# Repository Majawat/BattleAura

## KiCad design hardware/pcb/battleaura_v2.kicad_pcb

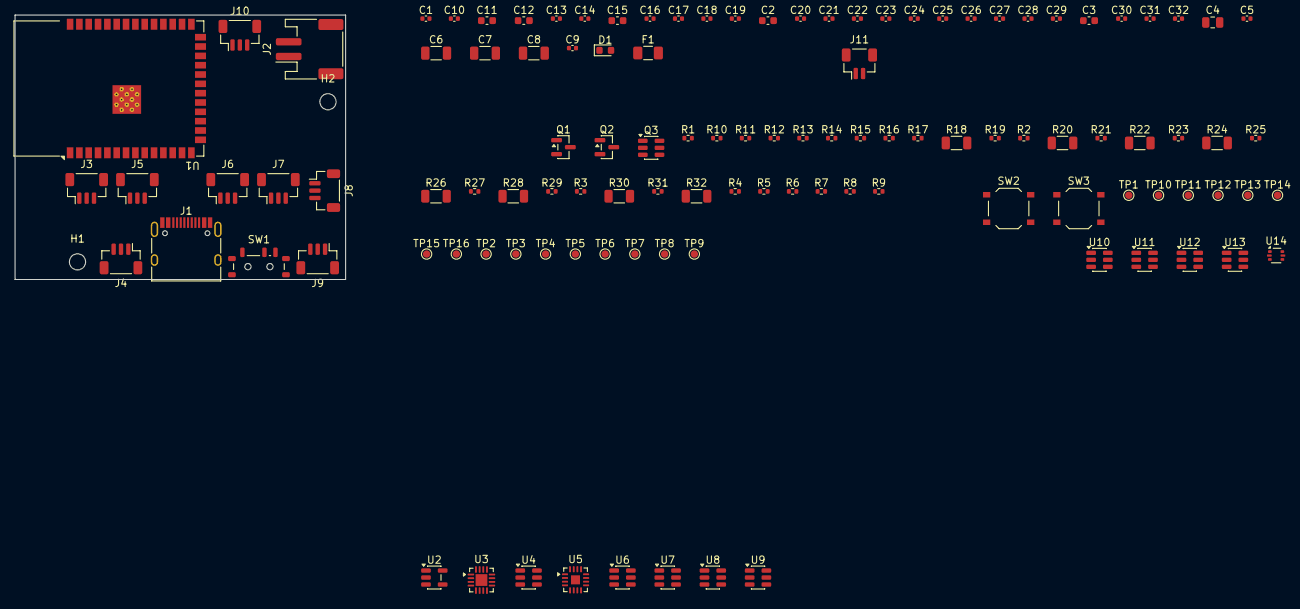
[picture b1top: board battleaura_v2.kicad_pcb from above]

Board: 2 copper layers, 45.0 x 36.0 mm, 115 parts (0 on the bottom side), 73 nets, no tracks yet.

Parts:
C1, C9, C13, C16, C17, C18, C19, C20, C21, C22, C23, C24, C25, C26, C27, C28, C29, C30, C31, C32: 100n; C_0402_1005Metric
C2, C3, C12, C15: 10u; C_0603_1608Metric
C4: 22u; C_0805_2012Metric
C5, C10, C14: 1u; C_0402_1005Metric
C6, C7, C8: 100u 10V; C_1206_3216Metric
C11: 22u; C_0603_1608Metric
D1: red; LED_0603_1608Metric
F1: 0.75A hold; Fuse_1206_3216Metric
H1, H2: MountingHole_2.2mm_M2
J1: USB_C_Receptacle_USB2.0_16P; USB_C_Receptacle_HRO_TYPE-C-31-M-12
J2: BATT; JST_PH_S2B-PH-SM4-TB_1x02-1MP_P2.00mm_Horizontal
J3: Z1; JST_SH_BM03B-SRSS-TB_1x03-1MP_P1.00mm_Vertical
J4: Z2; JST_SH_BM03B-SRSS-TB_1x03-1MP_P1.00mm_Vertical
J5: Z3; JST_SH_BM03B-SRSS-TB_1x03-1MP_P1.00mm_Vertical
J6: Z4; JST_SH_BM03B-SRSS-TB_1x03-1MP_P1.00mm_Vertical
J7: Z5; JST_SH_BM03B-SRSS-TB_1x03-1MP_P1.00mm_Vertical
J8: Z6; JST_SH_BM03B-SRSS-TB_1x03-1MP_P1.00mm_Vertical
J9: Z7; JST_SH_BM03B-SRSS-TB_1x03-1MP_P1.00mm_Vertical
J10: Z8; JST_SH_BM03B-SRSS-TB_1x03-1MP_P1.00mm_Vertical
J11: SPEAKER; JST_SH_BM02B-SRSS-TB_1x02-1MP_P1.00mm_Vertical
Q1, Q2: AO3401A; SOT-23
Q3: FS8205A; SOT-23-6
R1: 100; R_0402_1005Metric
R2, R10, R16: 1k; R_0402_1005Metric
R3, R4: 5.1k; R_0402_1005Metric
R5: 1.8k; R_0402_1005Metric
R6: 1.1k; R_0402_1005Metric
R7, R13: 10k; R_0402_1005Metric
R8: 1M; R_0402_1005Metric
R9, R12, R14, R15, R17, R19, R21, R23, R25, R27, R29, R31: 100k; R_0402_1005Metric
R11: 200k; R_0402_1005Metric
R18, R20, R22, R24, R26, R28, R30, R32: 120; R_1206_3216Metric
SW1: SW_SPDT; SW_SPDT_Shouhan_MSK12C02
SW2: BOOT; SW_Push_1P1T_XKB_TS-1187A
SW3: RESET; SW_Push_1P1T_XKB_TS-1187A
TP1: TXD0; TestPoint_Pad_D1.0mm
TP2: RXD0; TestPoint_Pad_D1.0mm
TP3: 3V3; TestPoint_Pad_D1.0mm
TP4: GND; TestPoint_Pad_D1.0mm
TP5: EN; TestPoint_Pad_D1.0mm
TP6: IO0; TestPoint_Pad_D1.0mm
TP7: IO3; TestPoint_Pad_D1.0mm
TP8: IO18; TestPoint_Pad_D1.0mm
TP9: IO21; TestPoint_Pad_D1.0mm
TP10: IO38; TestPoint_Pad_D1.0mm
TP11: IO39; TestPoint_Pad_D1.0mm
TP12: IO40; TestPoint_Pad_D1.0mm
TP13: IO41; TestPoint_Pad_D1.0mm
TP14: IO42; TestPoint_Pad_D1.0mm
TP15: IO47; TestPoint_Pad_D1.0mm
TP16: IO48; TestPoint_Pad_D1.0mm
U1: ESP32-S3-WROOM-1-N16R8; ESP32-S3-WROOM-1
U2: TLV75733PDBV; SOT-23-5
U3: BQ24074RGT; VQFN-16-1EP_3x3mm_P0.5mm_EP1.6x1.6mm
U4: DW01A; SOT-23-6
U5: MAX98357A; TQFN-16-1EP_3x3mm_P0.5mm_EP1.23x1.23mm
U6, U7, U8, U9, U10, U11, U12, U13: SN74LVC1T45DBV; SOT-23-6
U14: USBLC6-2SC6; SOT-666

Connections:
+3V3: C11.1, C12.1, C13.1, C17.1, C19.1, C21.1, C23.1, C25.1, C27.1, C29.1, C31.1, R13.2, R14.2, R15.2, TP3.1, U1.2, U2.5, U6.1, U6.5, U7.1, U7.5, U8.1, U8.5, U9.1, U9.5, U10.1, U10.5, U11.1, U11.5, U12.1, U12.5, U13.1, U13.5
CELL_N: C1.2, J2.2, Q1.1, Q3.1, U4.6
CELL_P: J2.1, Q1.3
CHG_N: R14.1, U1.17, U3.9
EN: C14.1, R13.1, SW3.1, TP5.1, U1.3
GND: C2.2, C3.2, C4.2, C6.2, C7.2, C8.2, C9.2, C10.2, C11.2, C12.2, C13.2, C14.2, C15.2, C16.2, C17.2, C18.2, C19.2, C20.2, C21.2, C22.2, C23.2, C24.2, C25.2, C26.2, C27.2, C28.2, C29.2, C30.2, C31.2, C32.2, D1.1, J1.A1, J1.A12, J1.B1, J1.B12, J1.S1, J3.3, J4.3, J5.3, J6.3, J7.3, J8.3, J9.3, J10.3, Q3.3, R2.2, R3.2, R4.2, R5.2, R6.2, R7.2, R9.2, R12.2, R17.2, R19.2, R21.2, R23.2, R25.2, R27.2, R29.2, R31.2, SW2.2, SW3.2, TP4.1, U1.1, U1.40, U1.41, U2.2, U3.4, U3.6, U3.8, U3.17, U5.3, U5.11, U5.15, U5.17, U6.2, U7.2, U8.2, U9.2, U10.2, U11.2, U12.2, U13.2, U14.2
IO0: SW2.1, TP6.1, U1.27
unnamed: C1.1, R1.2, U4.5
unnamed: Q3.6, U4.1
unnamed: Q3.4, U4.3
unnamed: R2.1, U4.2
unnamed: J1.A5, R3.1
unnamed: J1.B5, R4.1
unnamed: R5.1, U3.16
unnamed: R6.1, U3.12
unnamed: R7.1, U3.1
unnamed: R9.1, SW1.1
unnamed: R10.1, SW1.3
unnamed: R16.1, U1.38
unnamed: D1.2, R16.2
unnamed: U1.19, U5.14
unnamed: U1.20, U5.16
unnamed: U1.21, U5.1
unnamed: U1.22, U5.4
unnamed: J11.1, U5.9
unnamed: J11.2, U5.10
unnamed: R18.1, U6.4
unnamed: R20.1, U7.4
unnamed: R22.1, U8.4
unnamed: R24.1, U9.4
unnamed: R26.1, U10.4
unnamed: R28.1, U11.4
unnamed: R30.1, U12.4
unnamed: R32.1, U13.4
unnamed: TP1.1, U1.37
unnamed: TP2.1, U1.36
unnamed: TP7.1, U1.15
unnamed: TP8.1, U1.11
unnamed: TP9.1, U1.23
unnamed: TP10.1, U1.31
unnamed: TP11.1, U1.32
unnamed: TP12.1, U1.33
unnamed: TP13.1, U1.34
unnamed: TP14.1, U1.35
unnamed: TP15.1, U1.24
unnamed: TP16.1, U1.25
PGOOD_N: R15.1, U1.18, U3.7
Q2_G: C5.1, Q2.1, R8.1, SW1.2
Q3_D: Q3.2, Q3.5
USB_D+: J1.A6, J1.B6, U1.14, U14.3, U14.4
USB_D-: J1.A7, J1.B7, U1.13, U14.1, U14.6
VBAT_RAW: C3.1, Q1.2, R1.1, U3.2, U3.3
VBAT_SENSE: C9.1, R11.2, R12.1, U1.39
VBAT_SW: C6.1, C7.1, C8.1, C10.1, C15.1, C16.1, C18.1, C20.1, C22.1, C24.1, C26.1, C28.1, C30.1, C32.1, F1.1, Q2.3, R11.1, U2.1, U2.3, U5.2, U5.7, U5.8, U6.6, U7.6, U8.6, U9.6, U10.6, U11.6, U12.6, U13.6
VBUS: C2.1, J1.A4, J1.A9, J1.B4, J1.B9, U3.13, U14.5
VSYS: C4.1, C5.2, Q2.2, R8.2, R10.2, U3.5, U3.10, U3.11
Z1_IN: R17.1, U1.4, U6.3
Z1_SIG: J3.2, R18.2
Z2_IN: R19.1, U1.5, U7.3
Z2_SIG: J4.2, R20.2
Z3_IN: R21.1, U1.6, U8.3
Z3_SIG: J5.2, R22.2
Z4_IN: R23.1, U1.7, U9.3
Z4_SIG: J6.2, R24.2
Z5_IN: R25.1, U1.8, U10.3
Z5_SIG: J7.2, R26.2
Z6_IN: R27.1, U1.9, U11.3
Z6_SIG: J8.2, R28.2
Z7_IN: R29.1, U1.10, U12.3
Z7_SIG: J9.2, R30.2
Z8_IN: R31.1, U1.12, U13.3
Z8_SIG: J10.2, R32.2
ZONE_V+: F1.2, J3.1, J4.1, J5.1, J6.1, J7.1, J8.1, J9.1, J10.1
